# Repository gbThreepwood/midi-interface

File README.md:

# MIDI interface

A MIDI interface for use with a microcontroller.

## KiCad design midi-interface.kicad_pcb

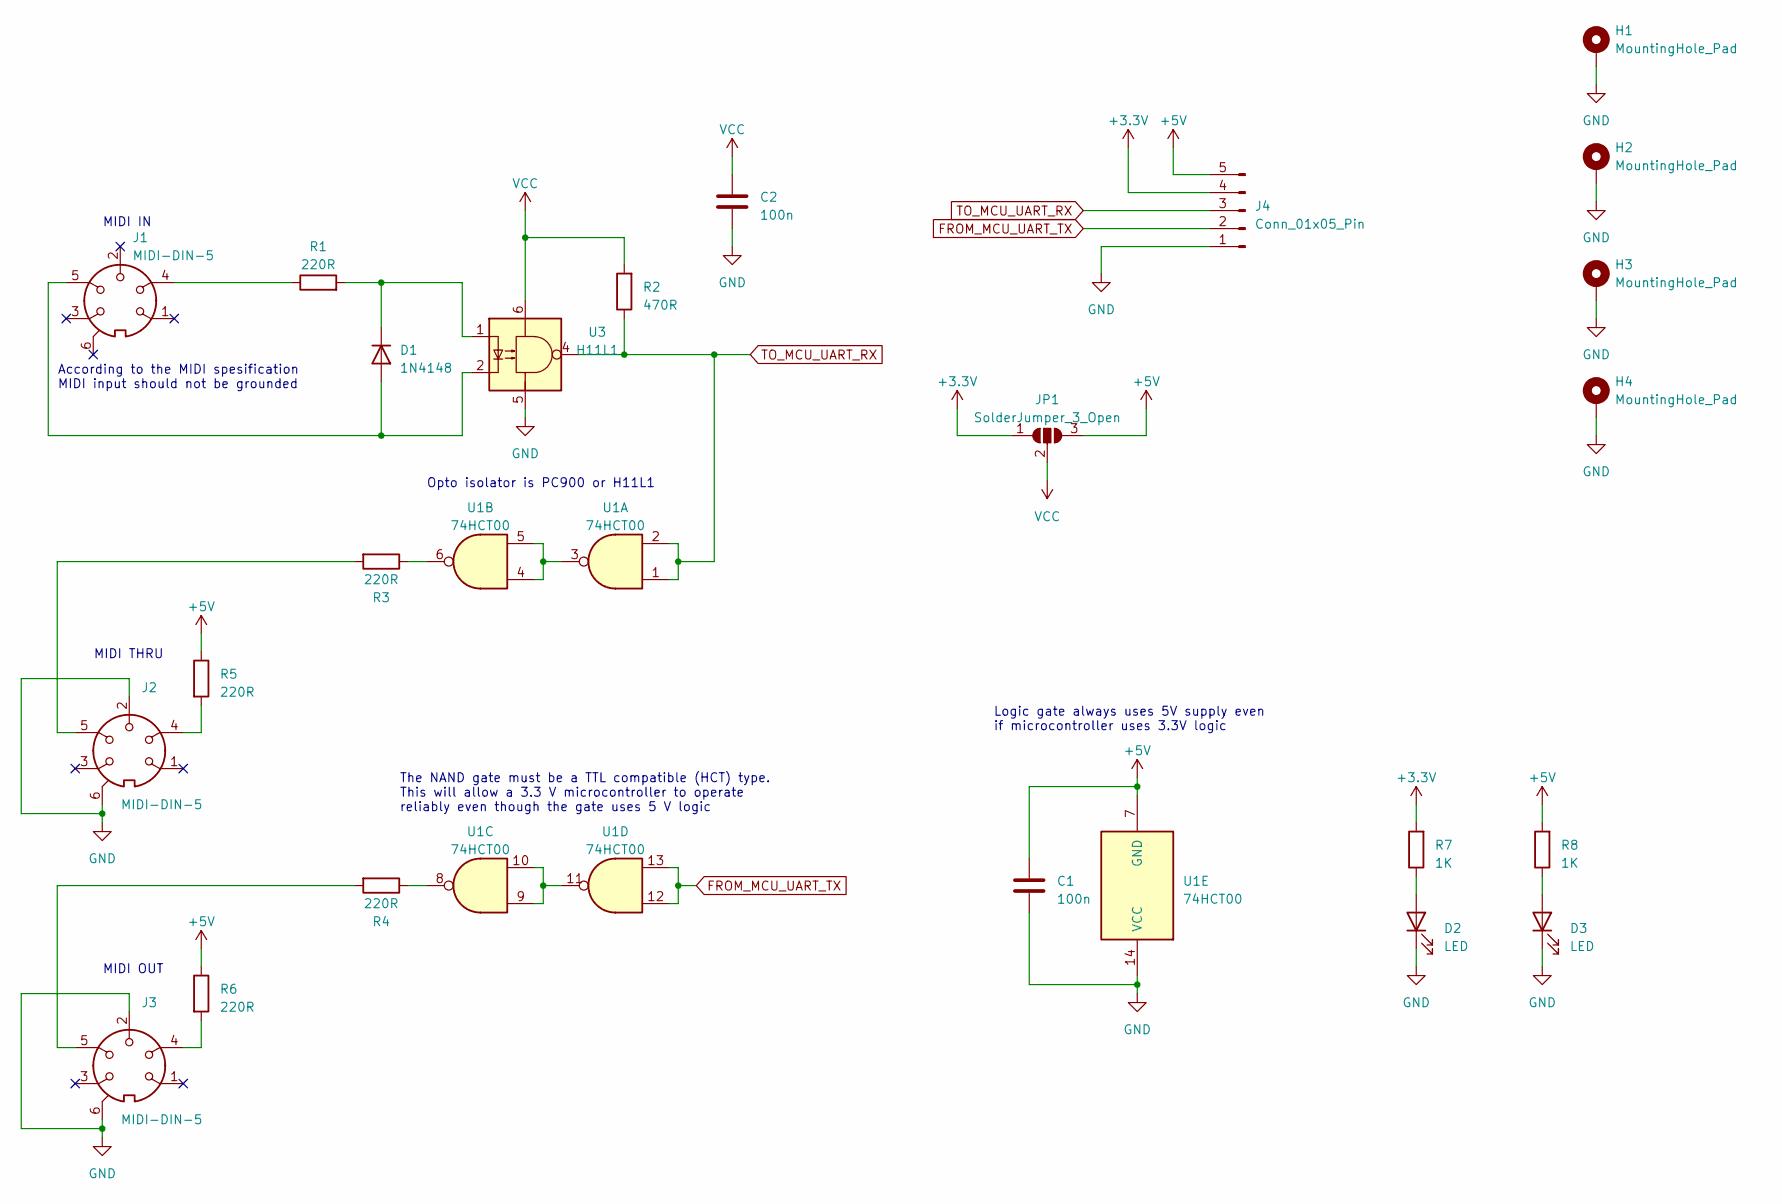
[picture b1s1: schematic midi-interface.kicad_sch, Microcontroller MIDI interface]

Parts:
C1, C2: 100n; C_1206_3216Metric_Pad1.33x1.80mm_HandSolder
D1: 1N4148; D_SOD-323_HandSoldering
D2, D3: LED; LED_1206_3216Metric_Pad1.42x1.75mm_HandSolder
H1, H2, H3, H4: MountingHole_Pad; MountingHole_3.2mm_M3_ISO7380_Pad_TopBottom
J1, J2, J3: MIDI-DIN-5; MIDI_DIN5_SCREEN
J4: Conn_01x05_Pin; PinHeader_1x05_P2.54mm_Vertical
JP1: SolderJumper_3_Open; SolderJumper-3_P1.3mm_Open_RoundedPad1.0x1.5mm
R1, R3, R4, R5, R6: 220R; R_1206_3216Metric_Pad1.30x1.75mm_HandSolder
R2: 470R; R_1206_3216Metric_Pad1.30x1.75mm_HandSolder
R7, R8: 1K; R_1206_3216Metric_Pad1.30x1.75mm_HandSolder
U1: 74HCT00; SSOP-14_5.3x6.2mm_P0.65mm
U3: H11L1; SO-6_4.4x3.6mm_P1.27mm

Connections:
+3.3V: J4.4, JP1.1 (A), R7.2
+5V: C1.1, J4.5, JP1.3 (B), R5.1, R6.1, R8.2, U1.7 (GND)
FROM_MCU_UART_TX: J4.2, U1.12, U1.13
GND: C1.2, C2.2, D2.1 (K), D3.1 (K), H1.1, H2.1, H3.1, H4.1, J2.2, J2.6, J3.2, J3.6, J4.1, U1.14 (VCC), U3.5
unnamed: D1.2 (A), J1.5, U3.2
unnamed: D1.1 (K), R1.2, U3.1
unnamed: D2.2 (A), R7.1
unnamed: D3.2 (A), R8.1
unnamed: J1.4, R1.1
unnamed: J2.4, R5.2
unnamed: J2.5, R3.2
unnamed: J3.4, R6.2
unnamed: J3.5, R4.2
unnamed: R3.1, U1.6
unnamed: R4.1, U1.8
unnamed: U1.3, U1.4, U1.5
unnamed: U1.9, U1.10, U1.11
TO_MCU_UART_RX: J4.3, R2.1, U1.1, U1.2, U3.4
VCC: C2.1, JP1.2 (C), R2.2, U3.6

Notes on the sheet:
According to the MIDI spesification MIDI input should not be grounded
Logic gate always uses 5V supply even if microcontroller uses 3.3V logic
MIDI OUT
The NAND gate must be a TTL compatible (HCT) type. This will allow a 3.3 V microcontroller to operate reliably even though the gate uses 5 V logic
MIDI IN
Opto isolator is PC900 or H11L1
MIDI THRU

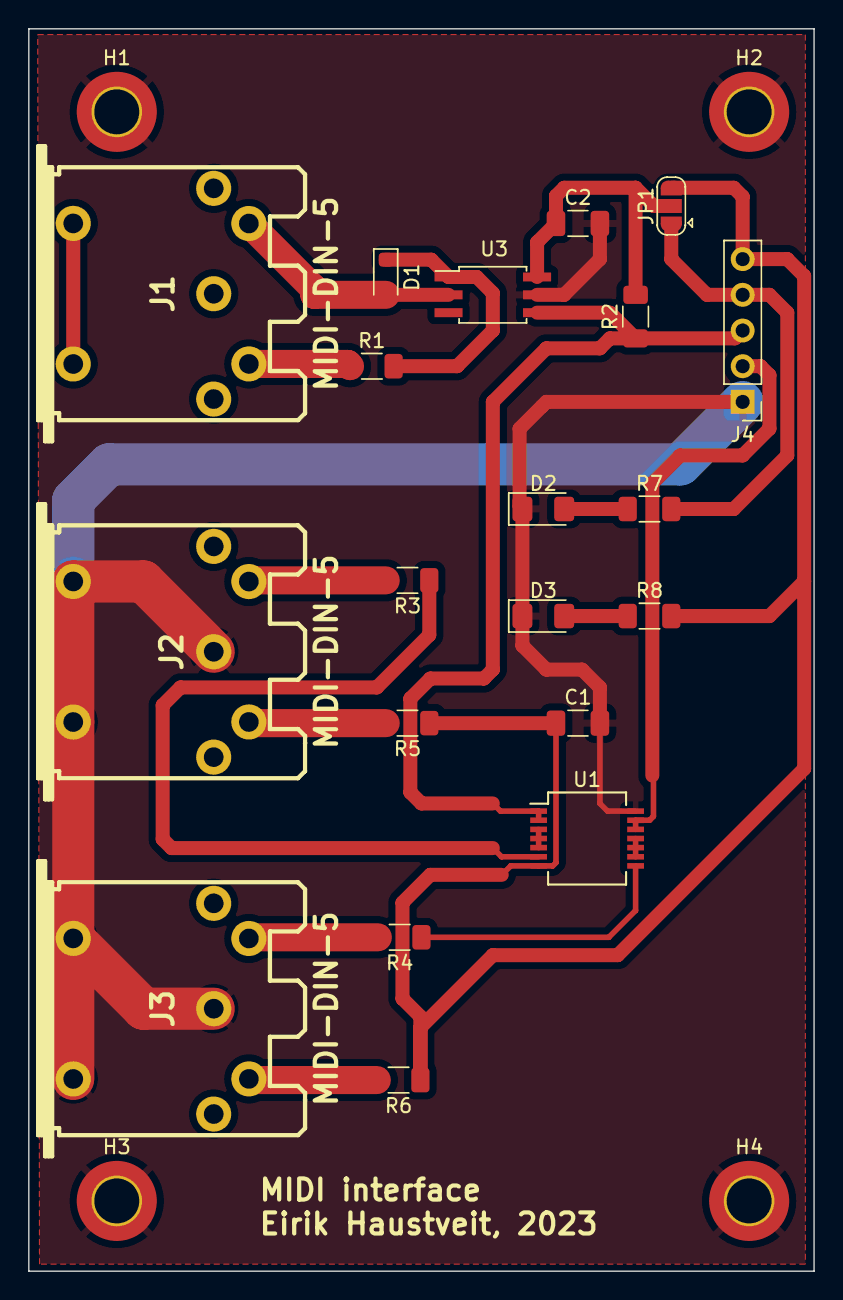
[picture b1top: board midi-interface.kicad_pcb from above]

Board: 2 copper layers, 55.9 x 88.4 mm, 24 parts (0 on the bottom side), 19 nets.

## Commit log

2024-10-17 Initial commit of README.md
2024-10-17 Initial KiCad design
2024-10-17 Updated design
2026-01-06 Small update
